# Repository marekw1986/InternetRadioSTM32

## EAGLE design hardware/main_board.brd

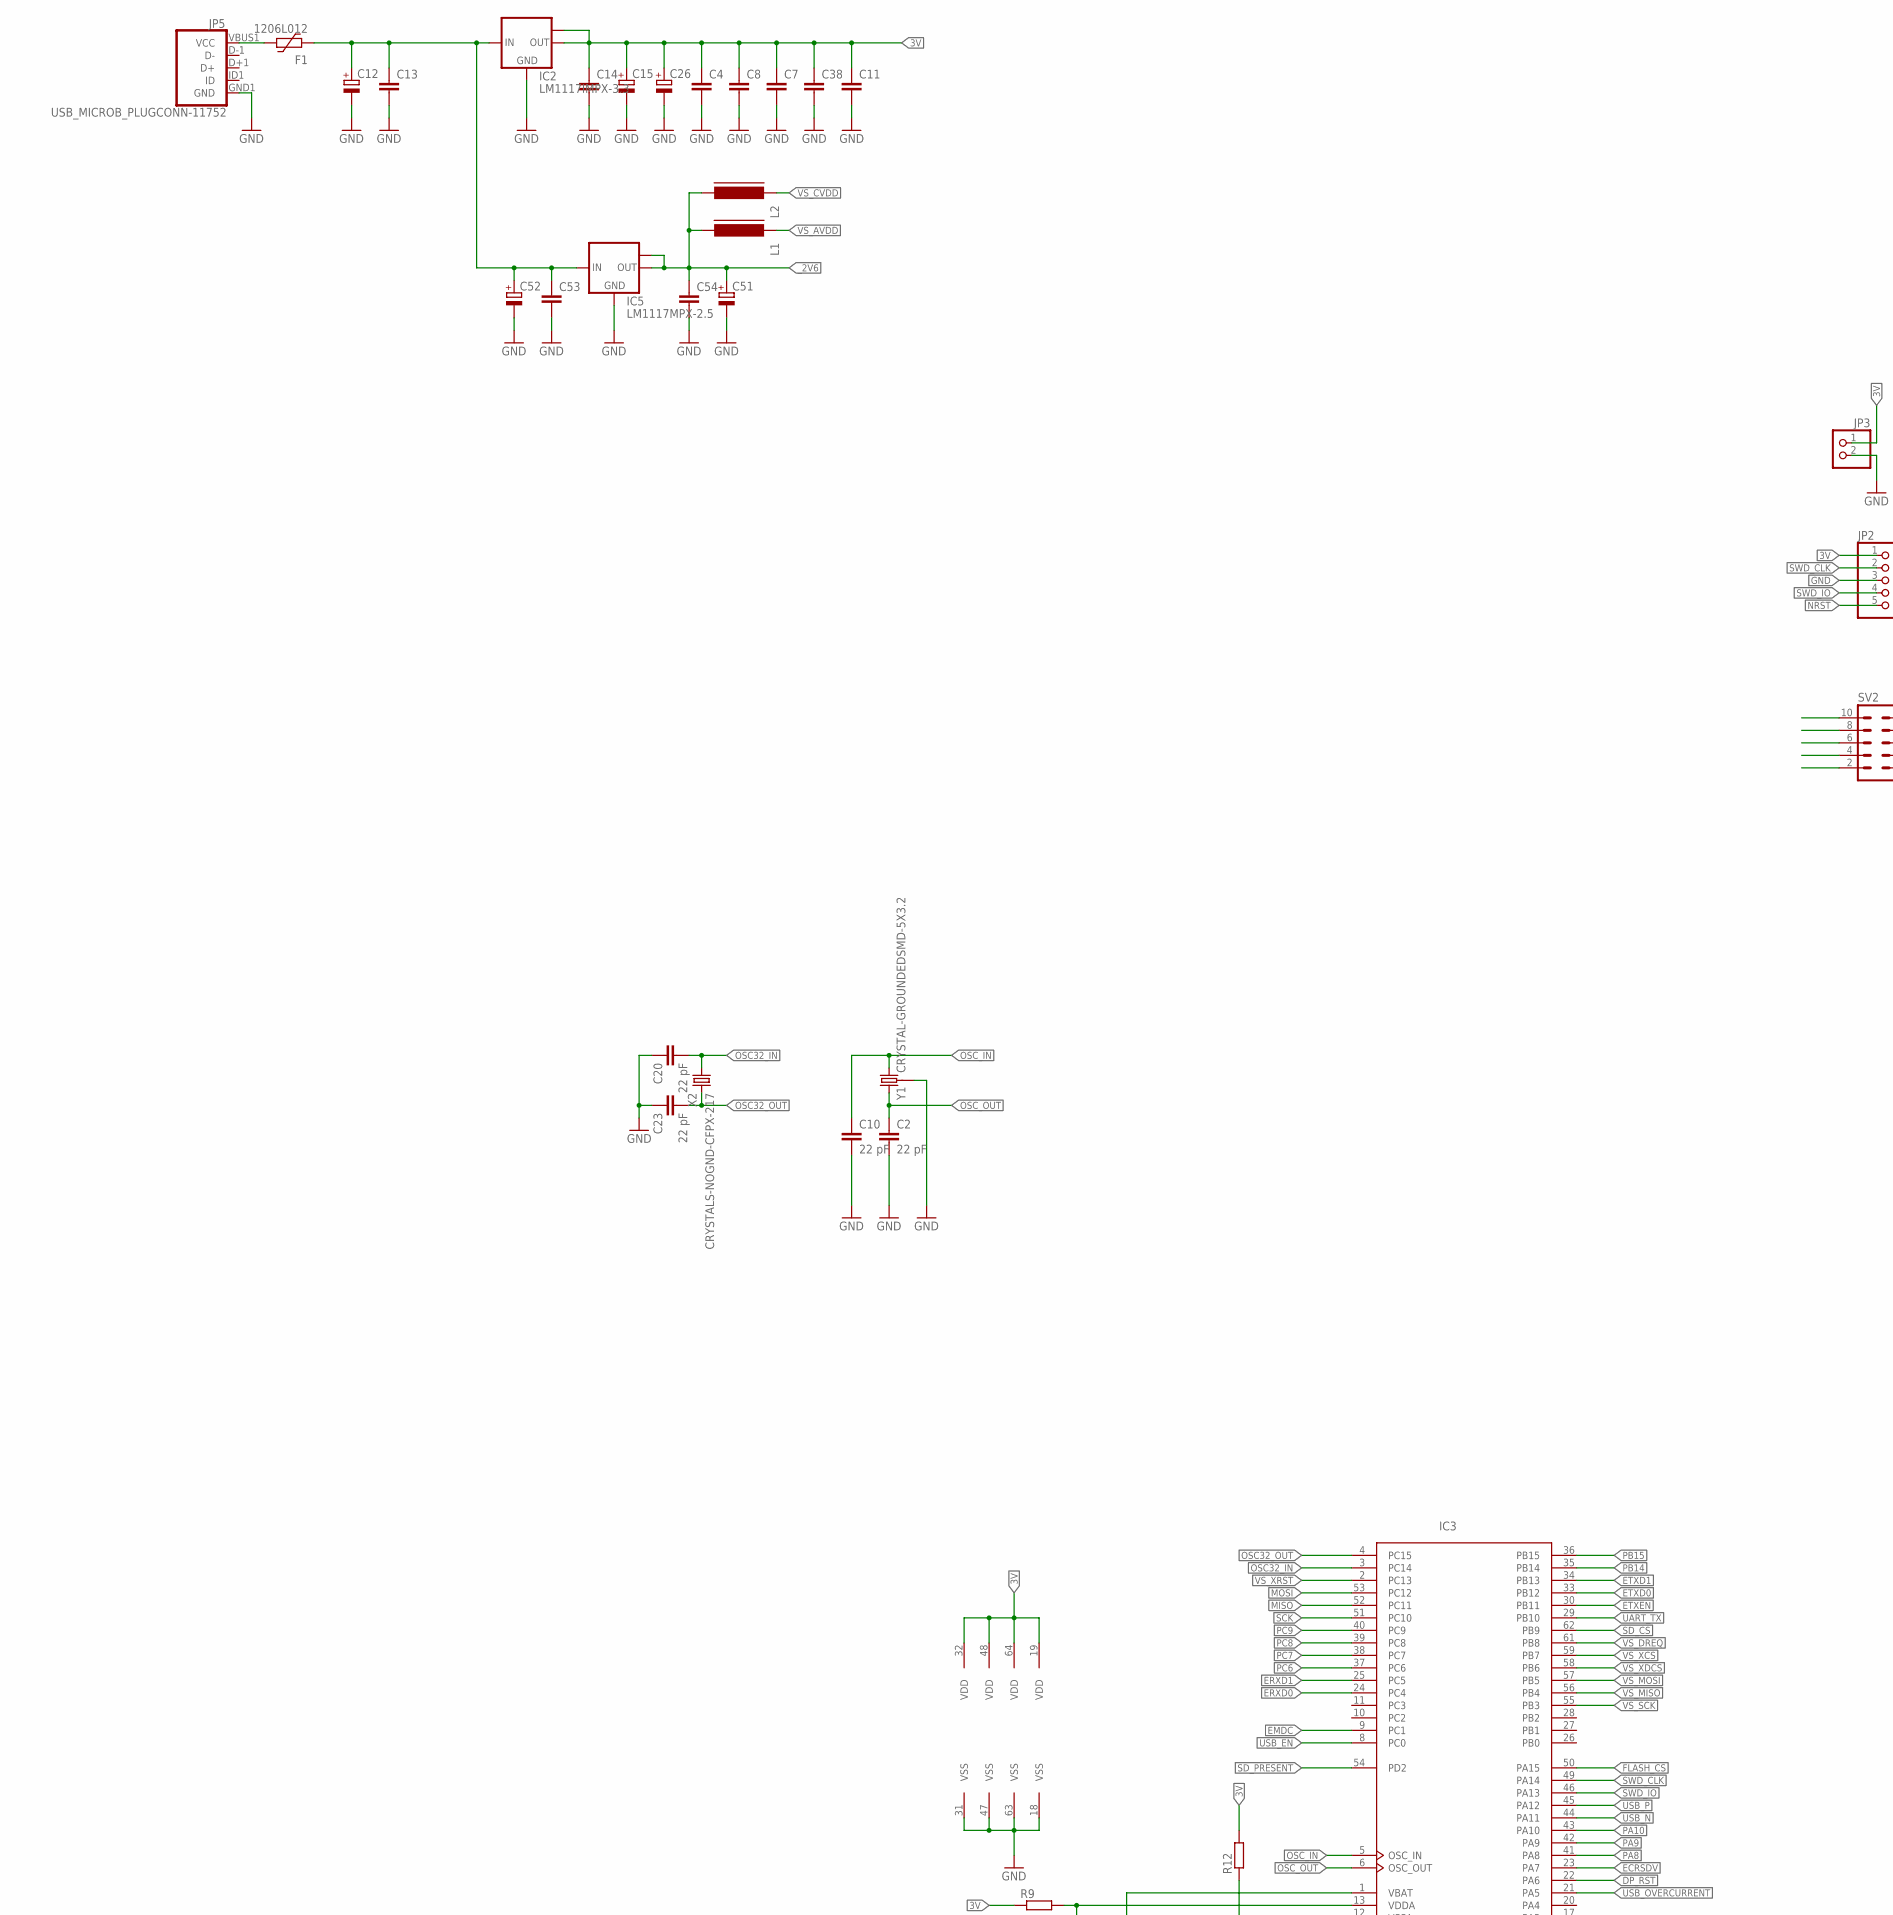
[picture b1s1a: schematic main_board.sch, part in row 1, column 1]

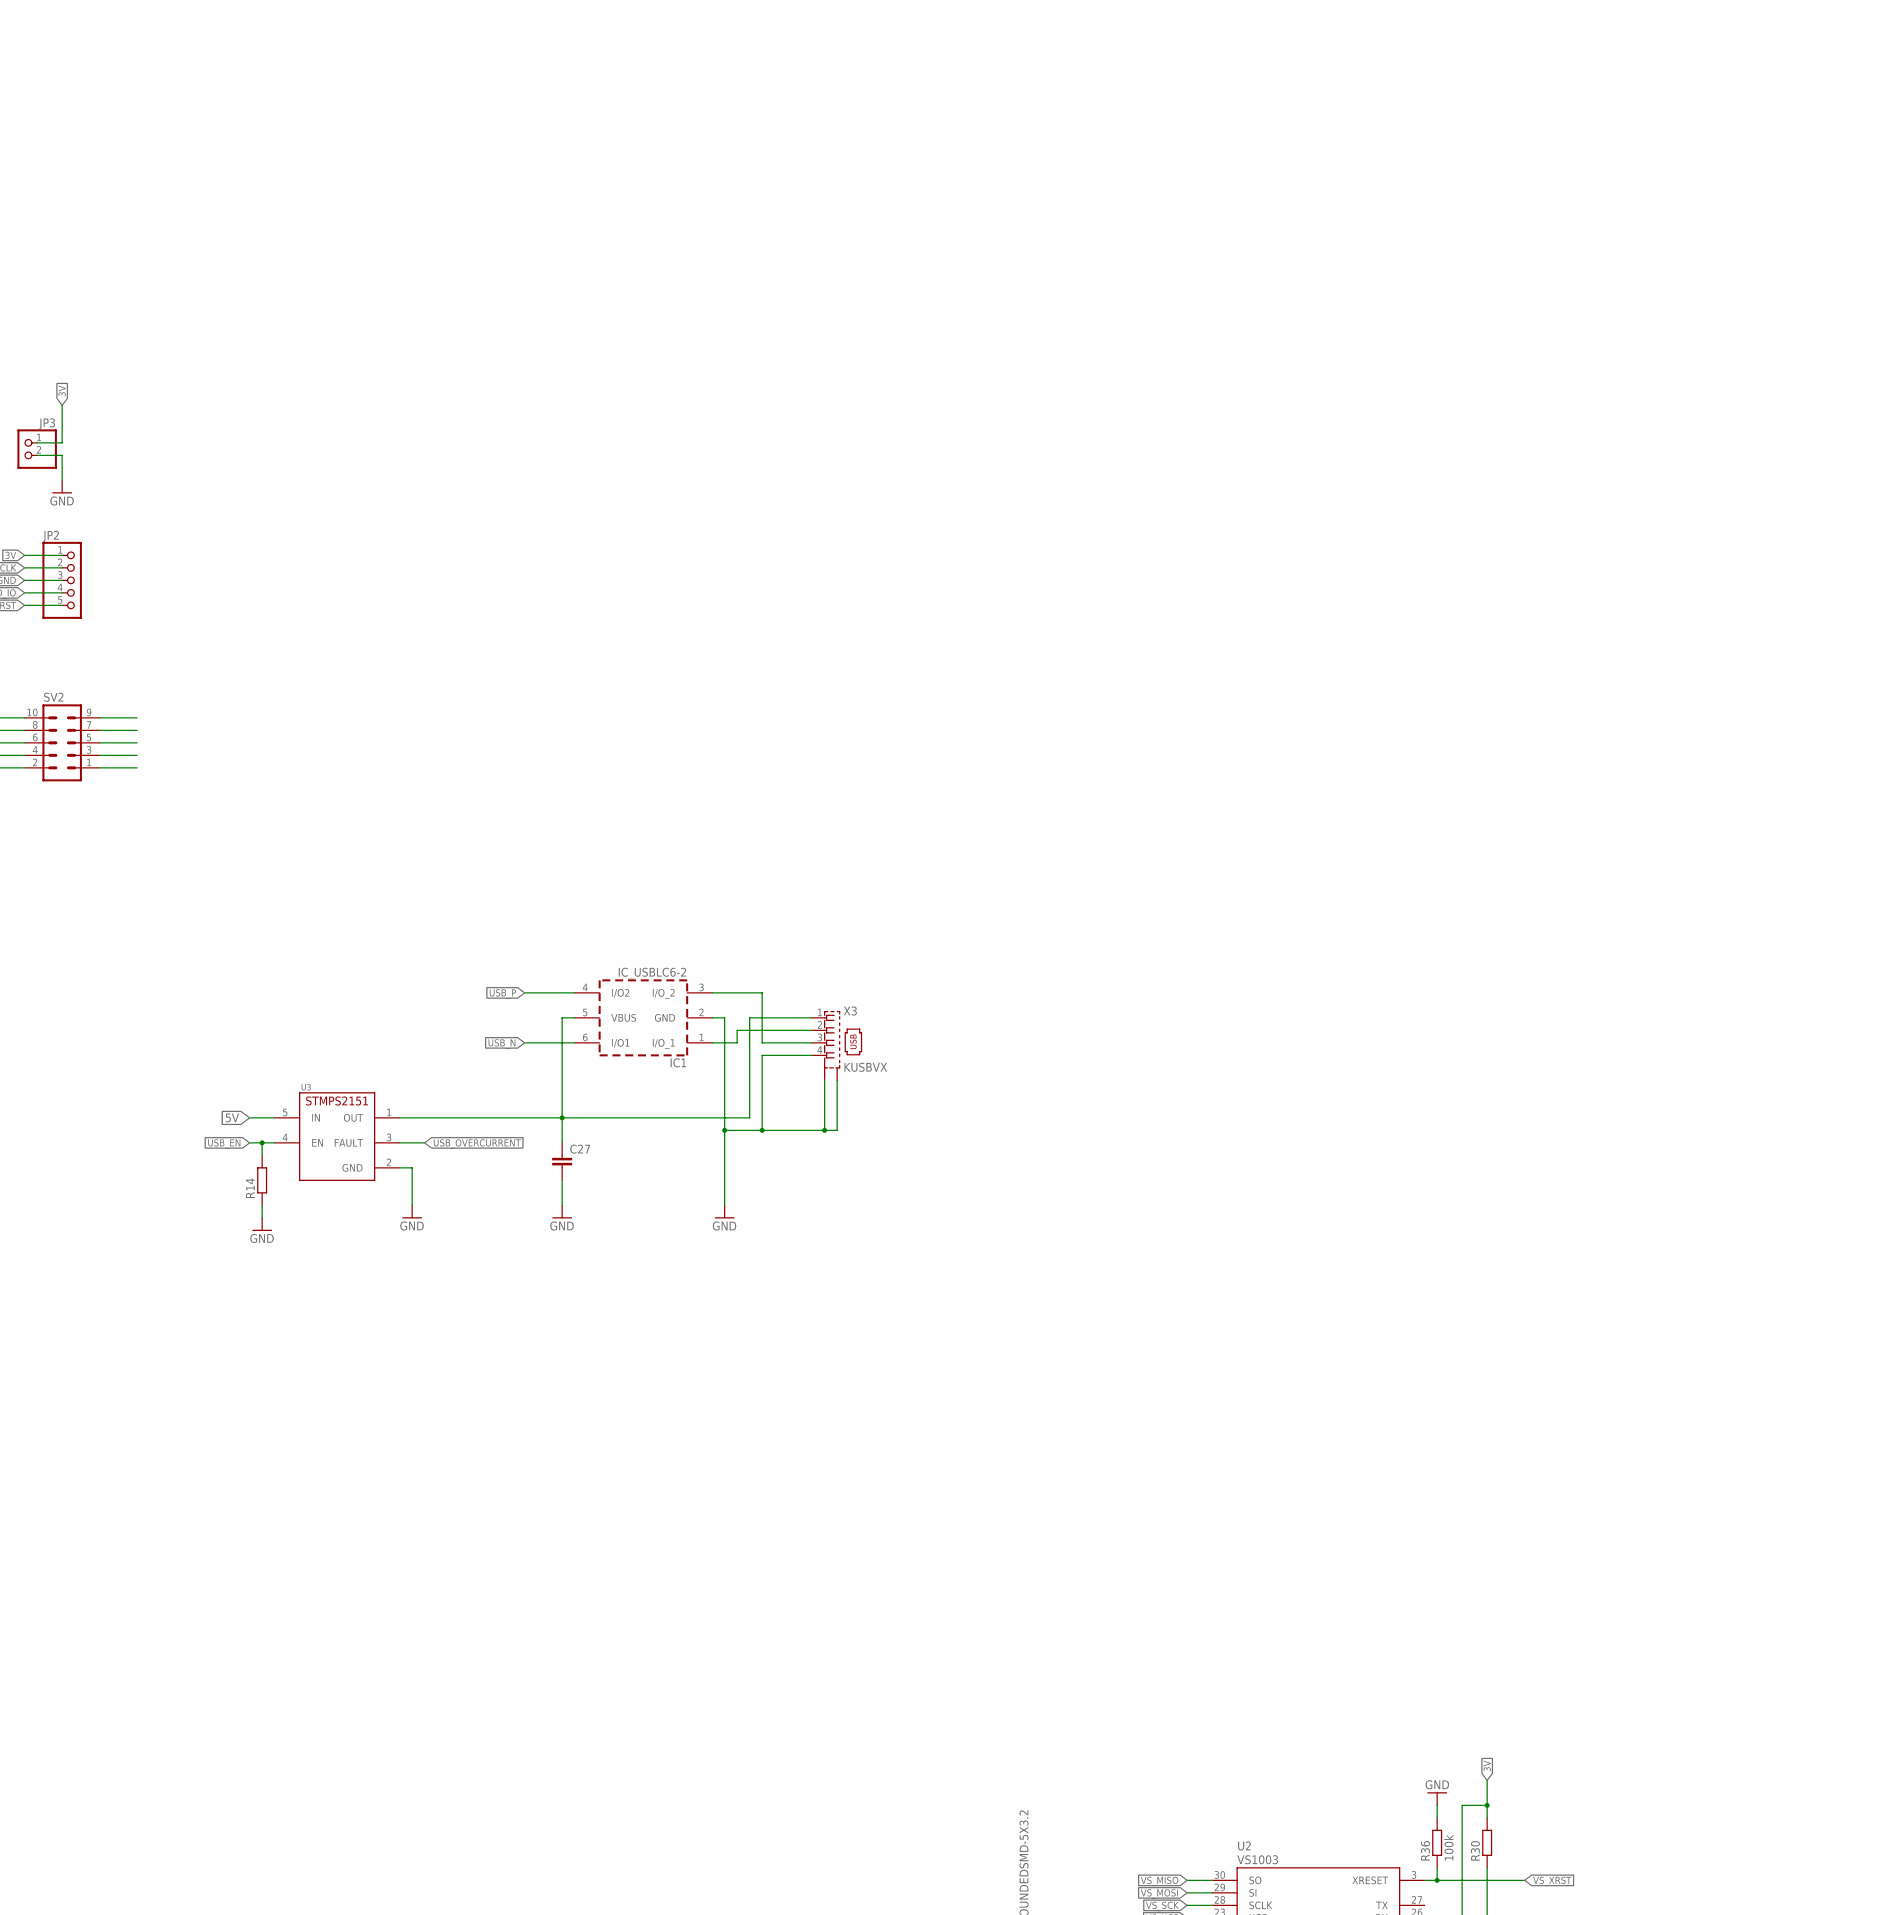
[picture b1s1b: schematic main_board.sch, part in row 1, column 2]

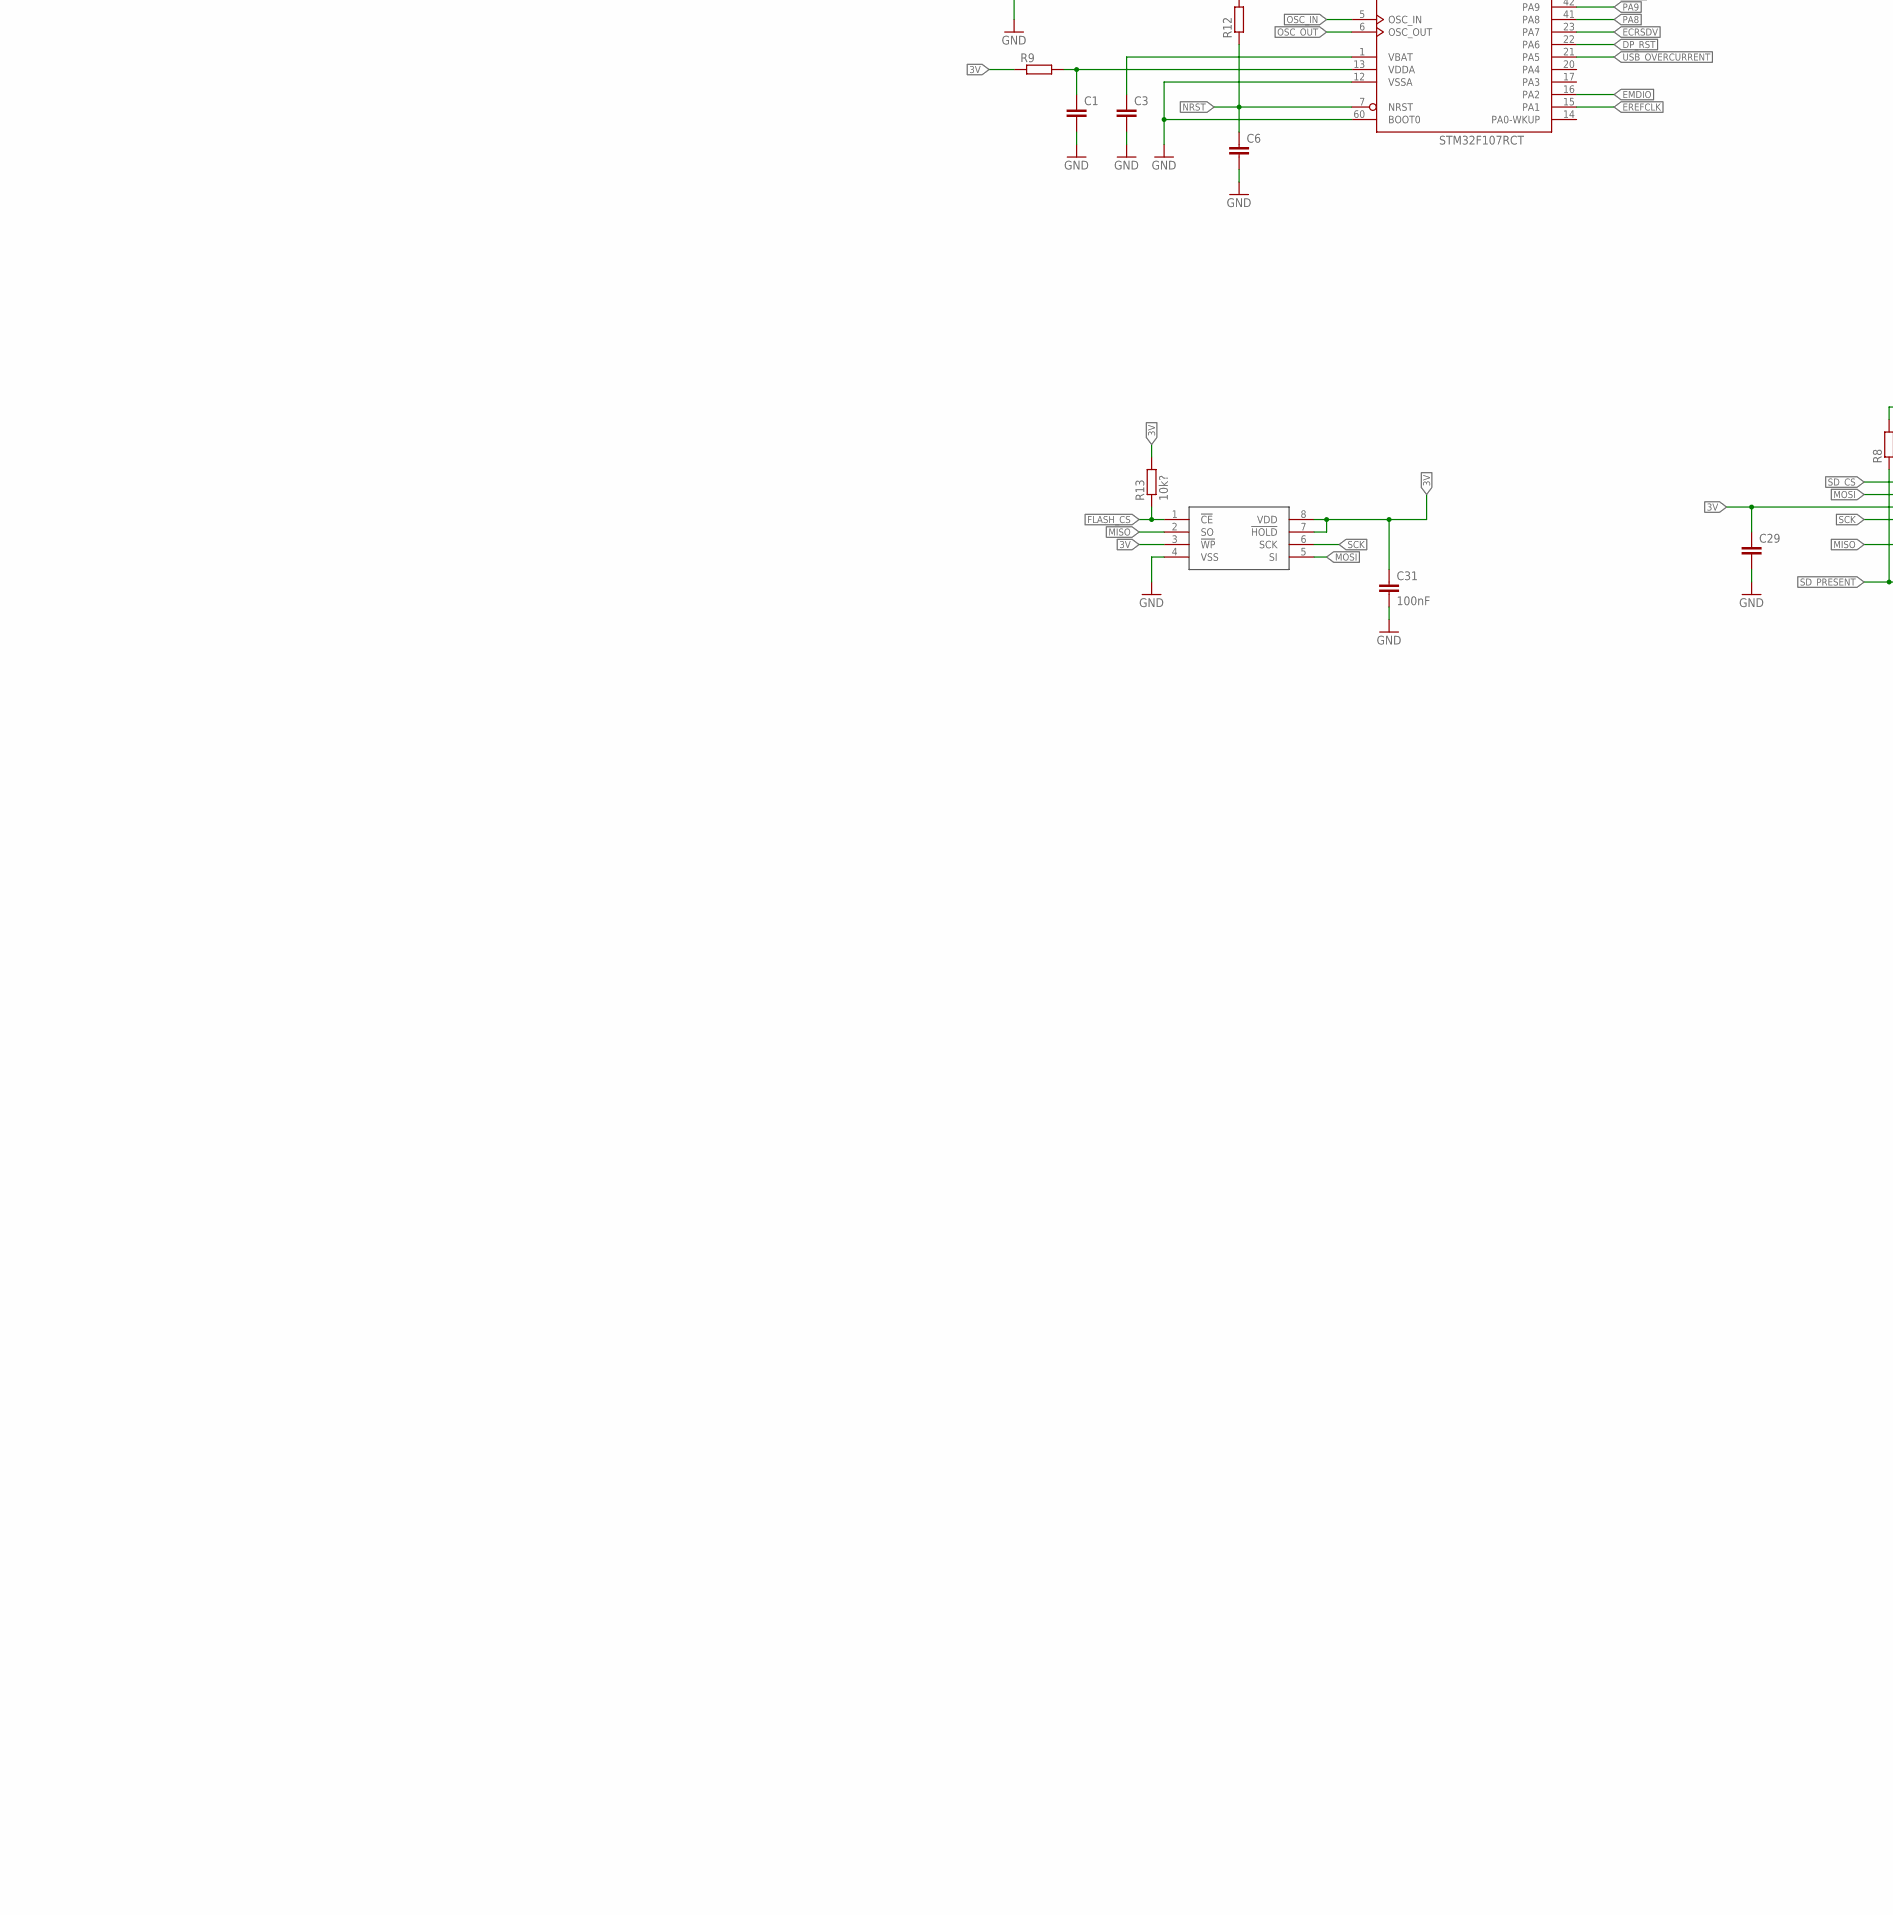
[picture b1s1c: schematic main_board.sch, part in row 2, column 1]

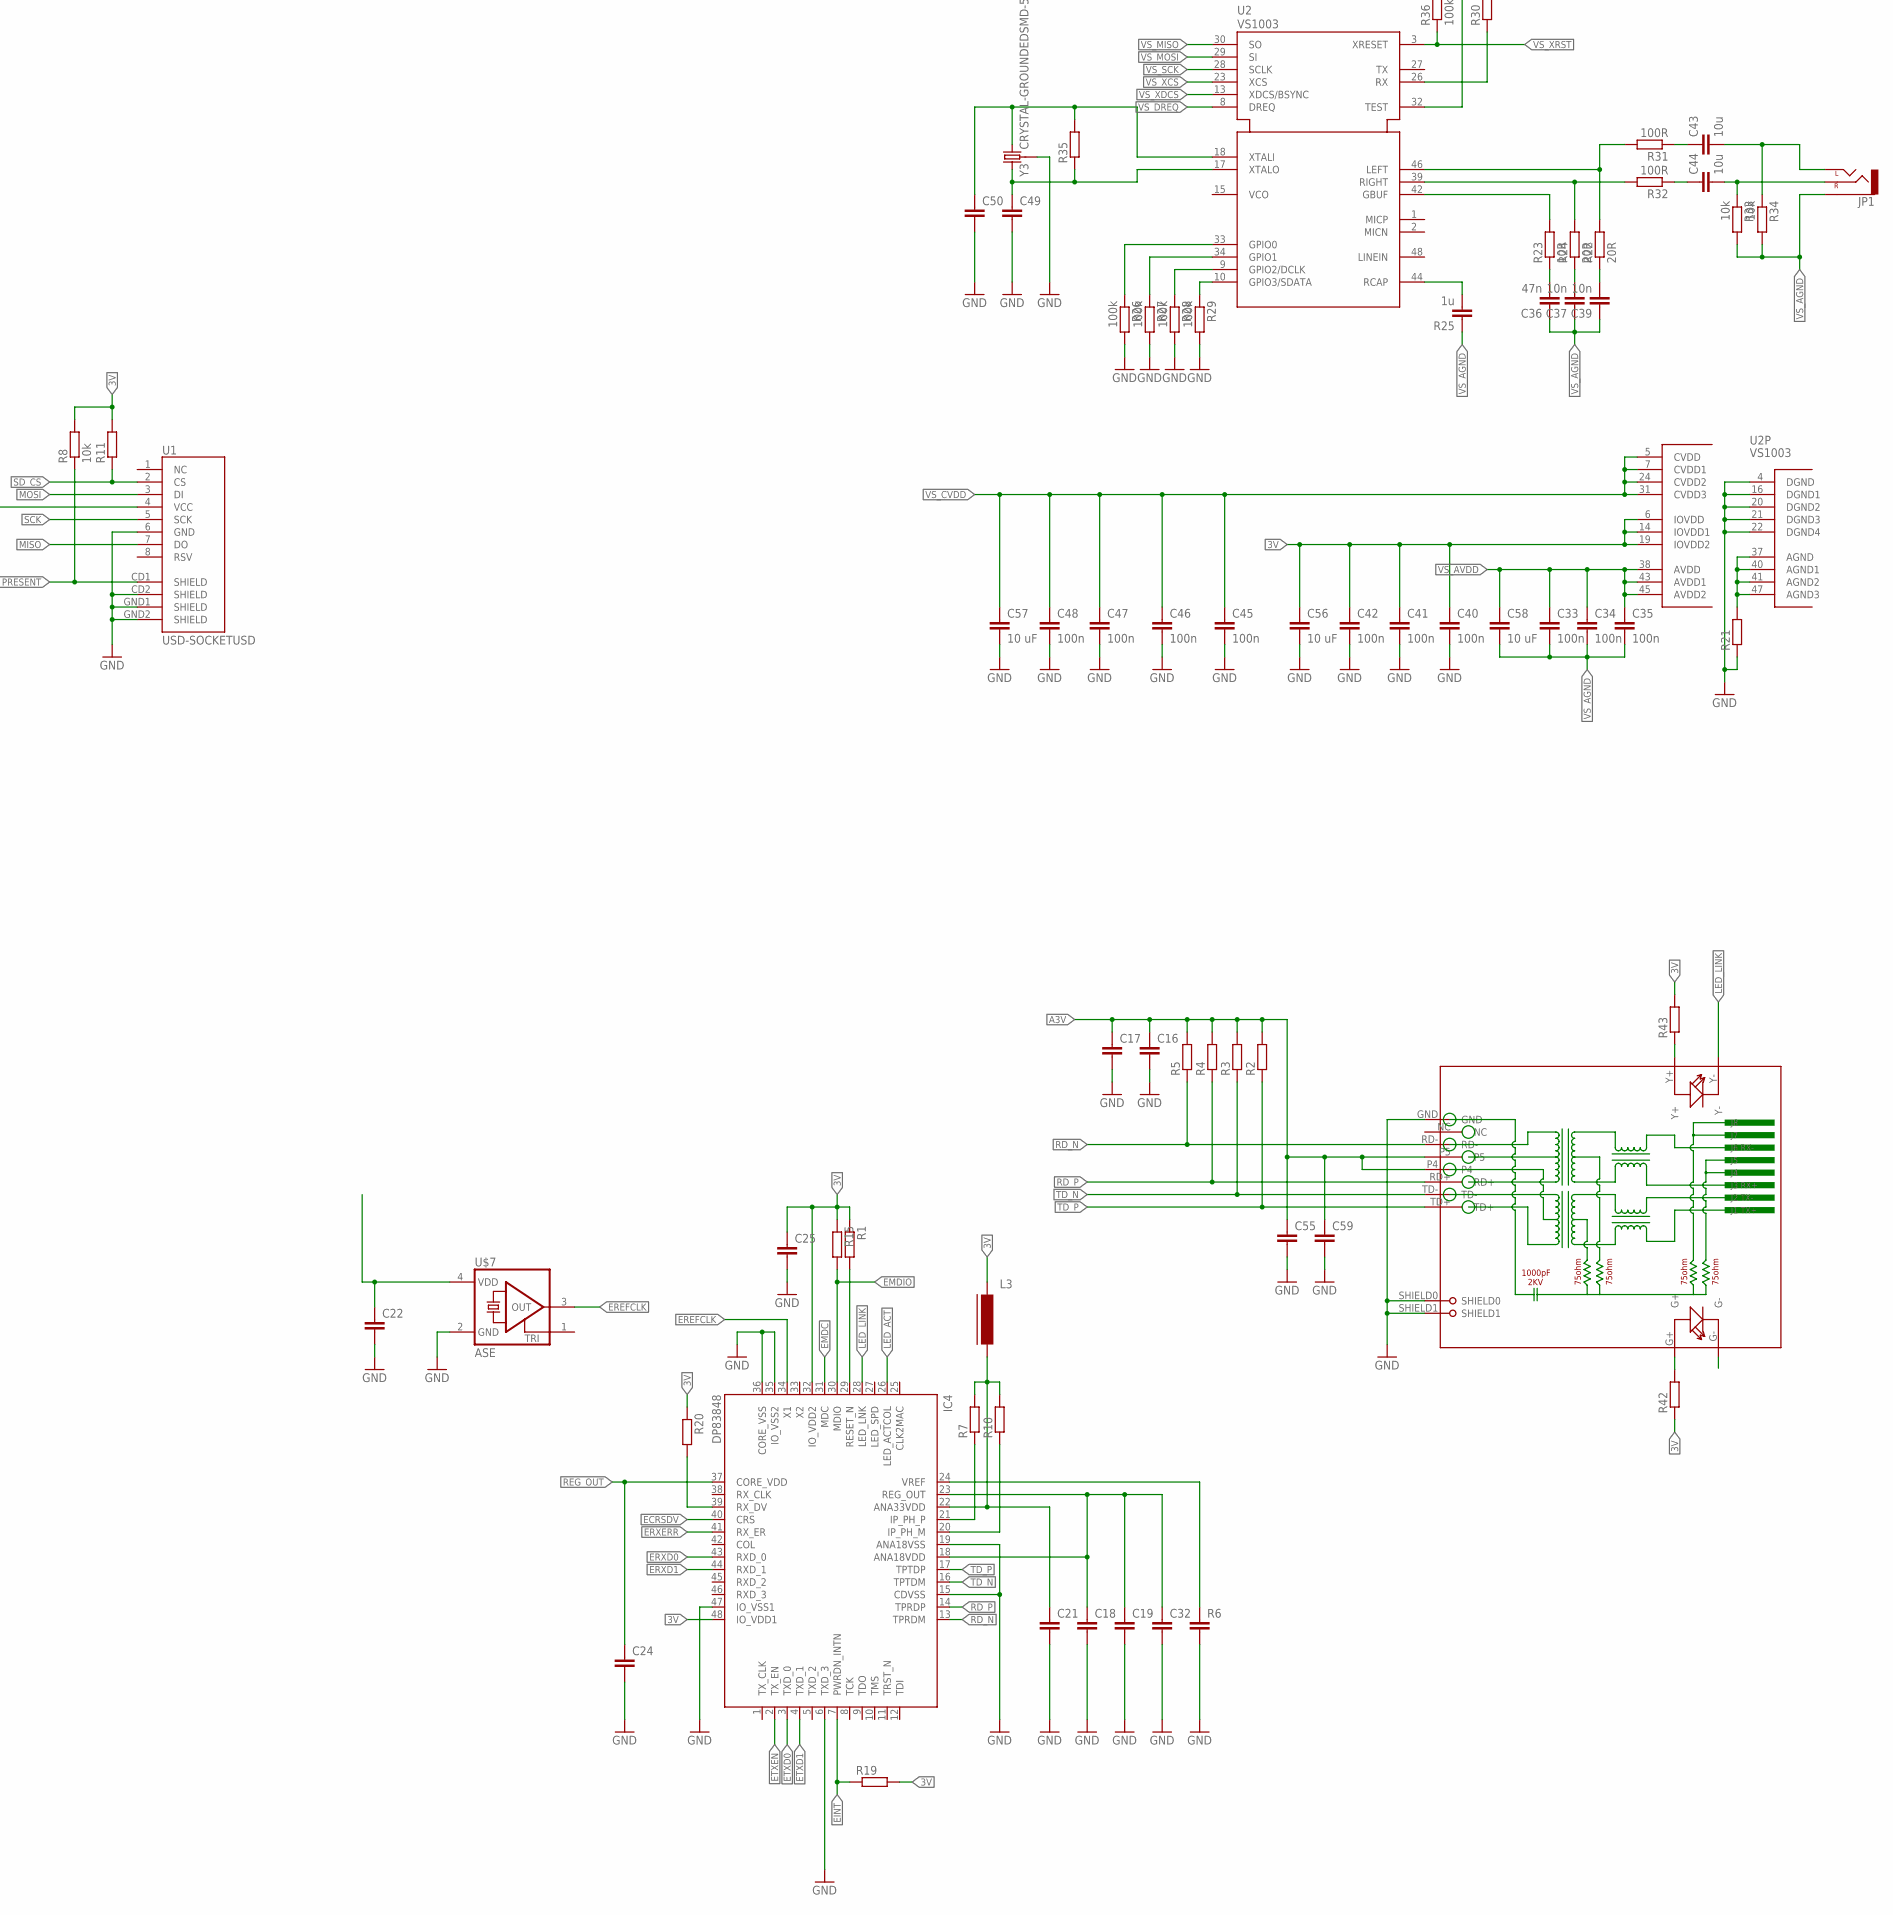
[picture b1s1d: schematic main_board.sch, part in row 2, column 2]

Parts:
C1, C3, C4, C7, C8, C11, C18, C19, C21, C22, C38: C-EUC0402; C0402
C2, C10, C20, C23: 22 pF; C0603
C6, C13, C14, C16, C17, C24, C25, C27, C29, C32, C49, C50, C55, C59: C-EUC0603; C0603
C12, C15, C51, C52: CPOL-EUSMCB; SMC_B
C26: CPOL-EUSMCA; SMC_A
C31: 100nF; C0603
C33, C34, C35, C46, C47, C48: 100n; C0603
C36: 47n; C0603
C37, C39: 10n; C0603
C40, C41, C42, C45: 100n; C0402
C43, C44: 10u; C0603
C53, C54: C-EUC1206; C1206
C56, C57, C58: 10 uF; C0603
F1: 1206L012; 1206L
IC1: IC_USBLC6-2; SOT-23-6L
IC2: LM1117IMPX-3.3; SOT223
IC3: STM32F107RCT; LQFP64
IC4: DP83848; LQFP48
IC5: LM1117MPX-2.5; SOT223
JP1: AUDIO-JACKAUDIO_JACK2; AUDIO-JACK2
JP2: PINHD-1X5; 1X05
JP3: PINHD-1X2/90; 1X02/90
JP5: USB_MICROB_PLUGCONN-11752; USB-B-MICRO-SMD_V03
L1, L2, L3: FERRITE-0805; FB805
R1, R7, R10, R19: R-EU_R0402; R0402
R2, R3, R4, R5, R11, R12, R14, R15, R20, R21, R35, R42, R43: R-EU_R0603; R0603
R6: C-EUC0603; C0603
R8, R33, R34: 10k; R0603
R9: R-EU_M0805; M0805
R13: 10k?; R0603
R22, R24: 20R; R0603
R23: 10R; R0603
R25: 1u; C0603
R26, R27, R28, R29: 100k; R0402
R30: R-EU_0204/7; 0204/7
R31, R32: 100R; R0603
R36: 100k; R0603
RJ1: HR911105A
SV2: ML10L
U1: USD-SOCKETUSD; USD-SOCKET-PP
U2: VS1003; LQFP48
U3: STMPS2151STR; SOT-23-5L
U$2: SST25VF016BSO8M; SO-08M
U$7: ASE
X2: CRYSTALS-NOGND-CFPX-217; 3.2X1.5-2-PAD
X3: KUSBVX
Y1, Y3: CRYSTAL-GROUNDEDSMD-5X3.2; CRYSTAL-SMD-5X3.2-4PAD

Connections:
3V: C4.1, C7.1, C8.1, C11.1, C14.1, C15.+, C22.1, C25.1, C26.+, C29.1, C31.1, C38.1, C40.1, C41.1, C42.1, C56.1, IC2.2 (OUT), IC2.TAB (OUT1), IC3.19 (VDD), IC3.32 (VDD), IC3.48 (VDD), IC3.64 (VDD), IC4.32 (IO_VDD2), IC4.48 (IO_VDD1), JP2.1, JP3.1, L3.1, R1.1, R8.2, R9.1, R11.2, R12.2, R13.2, R15.1, R19.2, R20.1, R30.2, R42.1, R43.2, U1.4 (VCC), U2.6 (IOVDD), U2.14 (IOVDD1), U2.19 (IOVDD2), U2.32 (TEST), U$2.3 (!WP), U$2.7 (!HOLD), U$2.8 (VDD), U$7.4 (VDD)
5V: C12.+, C13.1, C52.+, C53.1, F1.2, IC2.3 (IN), IC5.3 (IN), U3.5 (IN)
A3V: C16.1, C17.1, C21.1, C55.1, C59.1, IC4.22 (ANA33VDD), L3.2, R2.2, R3.2, R4.2, R5.2, R7.2, R10.2, RJ1.P4, RJ1.P5
D2_N: IC1.1 (I/O_1), X3.2
D2_P: IC1.3 (I/O_2), X3.3
DP_RST: IC3.22 (PA6), IC4.29 (RESET_N), R1.2
ECRSDV: IC3.23 (PA7), IC4.40 (CRS)
EINT: IC4.7 (PWRDN_INTN), R19.1
EMDC: IC3.9 (PC1), IC4.31 (MDC)
EMDIO: IC3.16 (PA2), IC4.30 (MDIO), R15.2
EREFCLK: IC3.15 (PA1), IC4.34 (X1), U$7.3 (OUT)
ERXD0: IC3.24 (PC4), IC4.43 (RXD_0)
ERXD1: IC3.25 (PC5), IC4.44 (RXD_1)
ERXERR: IC4.41 (RX_ER)
ETXD0: IC3.33 (PB12), IC4.3 (TXD_0)
ETXD1: IC3.34 (PB13), IC4.4 (TXD_1)
ETXEN: IC3.30 (PB11), IC4.2 (TX_EN)
FLASH_CS: IC3.50 (PA15), R13.1, U$2.1 (!CE)
GND: C1.2, C2.2, C3.2, C4.2, C6.2, C7.2, C8.2, C10.2, C11.2, C12.-, C13.2, C14.2, C15.-, C16.2, C17.2, C18.2, C19.2, C20.1, C21.2, C22.2, C23.1, C24.2, C25.2, C26.-, C27.2, C29.2, C31.2, C32.2, C38.2, C40.2, C41.2, C42.2, C45.2, C46.2, C47.2, C48.2, C49.2, C50.2, C51.-, C52.-, C53.2, C54.2, C55.2, C56.2, C57.2, C59.2, IC1.2 (GND), IC2.1 (GND), IC3.12 (VSSA), IC3.18 (VSS), IC3.31 (VSS), IC3.47 (VSS), IC3.60 (BOOT0), IC3.63 (VSS), IC4.6 (TXD_3), IC4.15 (CDVSS), IC4.19 (ANA18VSS), IC4.35 (IO_VSS2), IC4.36 (CORE_VSS), IC4.47 (IO_VSS1), IC5.1 (GND), JP2.3, JP3.2, JP5.GND1 (GND), R6.2, R14.1, R21.1, R26.2, R27.2, R28.2, R29.2, R36.2, RJ1.GND, RJ1.SHIELD0, RJ1.SHIELD1, U1.6 (GND), U1.CD2 (SHIELD), U1.GND1 (SHIELD), U1.GND2 (SHIELD), U2.4 (DGND)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
LED_ACT: IC4.26 (LED_ACTCOL), RJ1.G-
LED_LINK: IC4.28 (LED_LNK), RJ1.Y-
MISO: IC3.52 (PC11), U1.7 (DO), U$2.2 (SO)
MOSI: IC3.53 (PC12), U1.3 (DI), U$2.5 (SI)
unnamed: IC4.21 (IP_PH_P), R7.1
unnamed: C3.1, IC3.1 (VBAT)
unnamed: IC4.24 (VREF), R6.1
unnamed: IC4.20 (IP_PH_M), R10.1
unnamed: R42.2, RJ1.G+
unnamed: F1.1, JP5.VBUS1 (VCC)
unnamed: C36.2, R23.1
unnamed: R43.1, RJ1.Y+
unnamed: C1.1, IC3.13 (VDDA), R9.2
NRST: C6.1, IC3.7 (NRST), JP2.5, R12.1
OSC32_IN: C20.2, IC3.3 (PC14), X2.1
OSC32_OUT: C23.2, IC3.4 (PC15), X2.2
OSC_IN: C10.1, IC3.5 (OSC_IN), Y1.1 (2)
OSC_OUT: C2.1, IC3.6 (OSC_OUT), Y1.3 (1)
PA8: IC3.41 (PA8), SV2.8
PA9: IC3.42 (PA9), SV2.9
PA10: IC3.43 (PA10), SV2.10
PB14: IC3.35 (PB14), SV2.2
PB15: IC3.36 (PB15), SV2.3
PC6: IC3.37 (PC6), SV2.4
PC7: IC3.38 (PC7), SV2.5
PC8: IC3.39 (PC8), SV2.6
PC9: IC3.40 (PC9), SV2.7
RD_N: IC4.13 (TPRDM), R5.1, RJ1.RD-
RD_P: IC4.14 (TPRDP), R4.1, RJ1.RD+
REG_OUT: C18.1, C19.1, C24.1, C32.1, IC4.18 (ANA18VDD), IC4.23 (REG_OUT), IC4.37 (CORE_VDD)
RX_DV: IC4.39 (RX_DV), R20.2
SCK: IC3.51 (PC10), U1.5 (SCK), U$2.6 (SCK)
SD_CS: IC3.62 (PB9), R11.1, U1.2 (CS)
SD_PRESENT: IC3.54 (PD2), R8.1, U1.CD1 (SHIELD)
SWD_CLK: IC3.49 (PA14), JP2.2
SWD_IO: IC3.46 (PA13), JP2.4
TD_N: IC4.16 (TPTDM), R3.1, RJ1.TD-
TD_P: IC4.17 (TPTDP), R2.1, RJ1.TD+
UART_TX: IC3.29 (PB10), SV2.1
USB_EN: IC3.8 (PC0), R14.2, U3.4 (EN)
USB_N: IC1.6 (I/O1), IC3.44 (PA11)
USB_OVERCURRENT: IC3.21 (PA5), U3.3 (FAULT)
USB_P: IC1.4 (I/O2), IC3.45 (PA12)
VBUS: C27.1, IC1.5 (VBUS), U3.1 (OUT), X3.1
VS_AGND: C33.2, C34.2, C35.2, C36.1, C37.1, C39.1, C58.2, JP1.SLEEVE, R21.2, R25.1, R33.2, R34.2, U2.37 (AGND), U2.40 (AGND1), U2.41 (AGND2), U2.47 (AGND3)
VS_AVDD: C33.1, C34.1, C35.1, C58.1, L1.1, U2.38 (AVDD), U2.43 (AVDD1), U2.45 (AVDD2)
VS_CVDD: C45.1, C46.1, C47.1, C48.1, C57.1, L2.1, U2.5 (CVDD), U2.7 (CVDD1), U2.24 (CVDD2), U2.31 (CVDD3)
VS_DREQ: IC3.61 (PB8), U2.8 (DREQ)
VS_MISO: IC3.56 (PB4), U2.30 (SO)
VS_MOSI: IC3.57 (PB5), U2.29 (SI)
VS_N$9: C50.1, R35.2, U2.18 (XTALI), Y3.1 (2)
VS_N$13: C49.1, R35.1, U2.17 (XTALO), Y3.3 (1)
VS_N$14: R22.2, R31.2, U2.46 (LEFT)
VS_N$15: R23.2, U2.42 (GBUF)
VS_N$16: R24.2, R32.2, U2.39 (RIGHT)
VS_N$17: R25.2, U2.44 (RCAP)
VS_N$24: C37.2, R24.1
VS_N$25: C39.2, R22.1
VS_N$26: R29.1, U2.10 (GPIO3/SDATA)
VS_N$27: R28.1, U2.9 (GPIO2/DCLK)
VS_N$28: R27.1, U2.34 (GPIO1)
VS_N$30: R26.1, U2.33 (GPIO0)
VS_N$34: R30.1, U2.26 (RX)
VS_N$35: C43.1, R31.1
VS_N$36: C44.1, R32.1
VS_N$37: C44.2, JP1.RING (RIGHT), R33.1
VS_N$38: C43.2, JP1.TIP (LEFT), R34.1
VS_SCK: IC3.55 (PB3), U2.28 (SCLK)
VS_XCS: IC3.59 (PB7), U2.23 (XCS)
VS_XDCS: IC3.58 (PB6), U2.13 (XDCS/BSYNC)
VS_XRST: IC3.2 (PC13), R36.1, U2.3 (XRESET)
_2V6: C51.+, C54.1, IC5.2 (OUT), IC5.TAB (OUT1), L1.2, L2.2

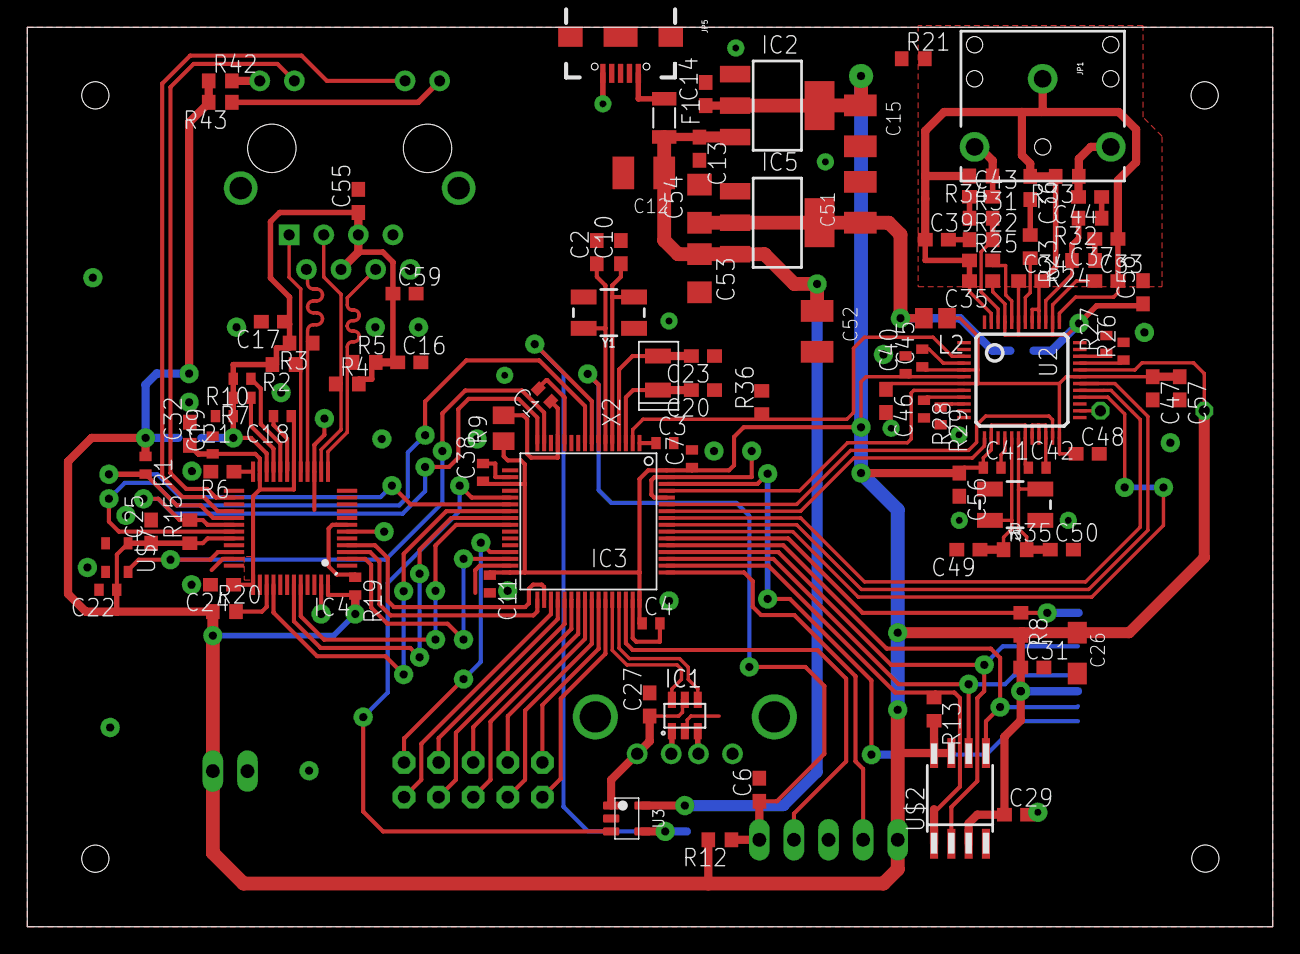
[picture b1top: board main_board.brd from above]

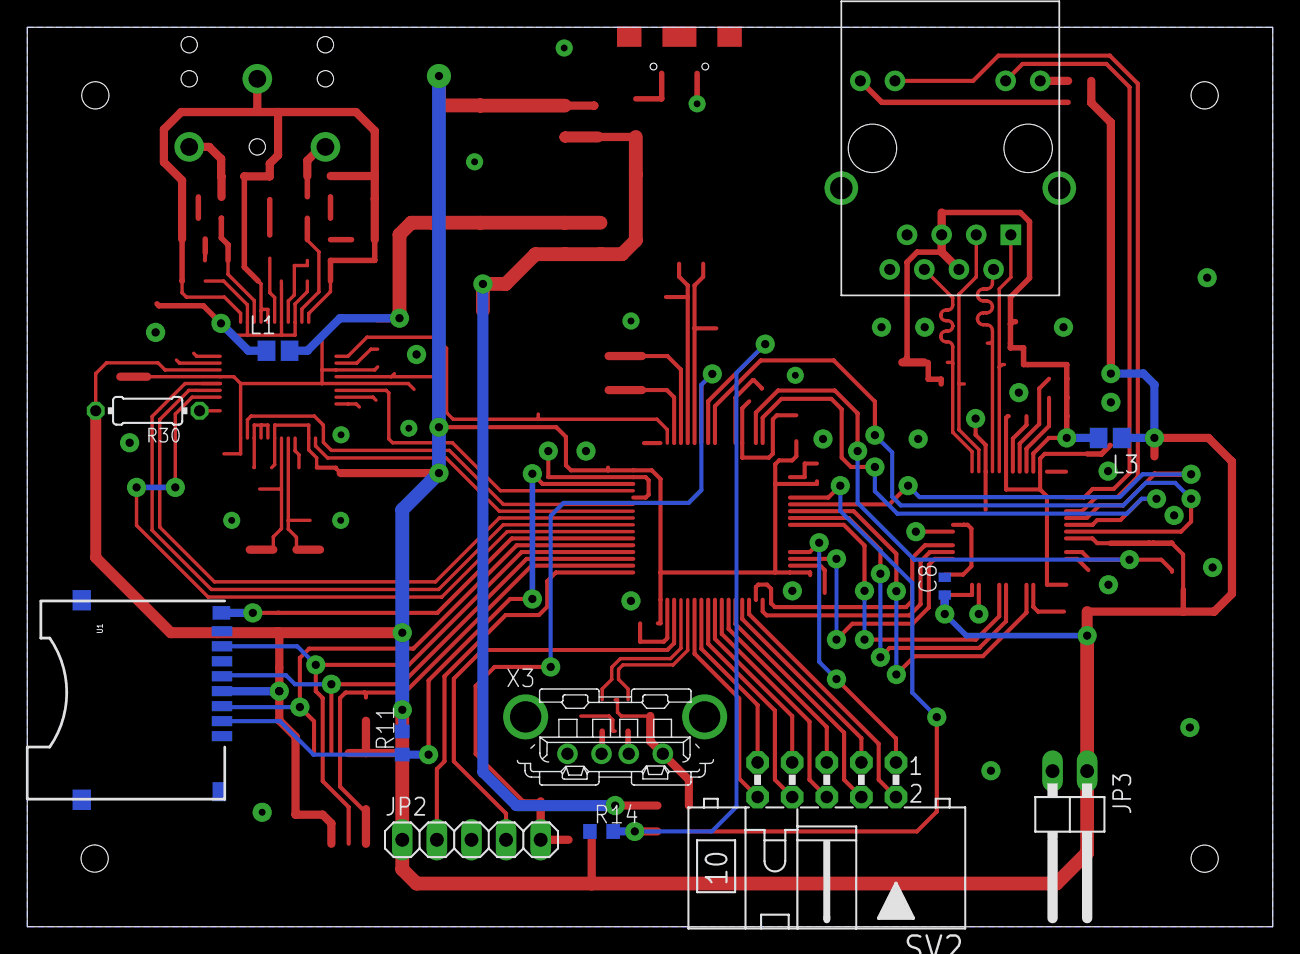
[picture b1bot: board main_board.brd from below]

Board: 2 copper layers, 91.4 x 66.0 mm, 114 parts (12 on the bottom side), 90 nets.

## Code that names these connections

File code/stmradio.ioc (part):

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Mcu.Name=STM32F107R(B-C)Tx
Mcu.Package=LQFP64
Mcu.UserName=STM32F107RCTx
PA1.Mode=RMII
PA1.Signal=ETH_REF_CLK
PA11.Mode=Host_Only
PA11.Signal=USB_OTG_FS_DM
PA12.Mode=Host_Only
PA12.Signal=USB_OTG_FS_DP
PA13.Mode=Serial_Wire
PA13.Signal=SYS_JTMS-SWDIO
PA14.Mode=Serial_Wire
PA14.Signal=SYS_JTCK-SWCLK
PA15.GPIOParameters=GPIO_Label
PA15.GPIO_Label=FLASH_CS
PA15.Signal=GPIO_Output
PA2.Mode=RMII
PA2.Signal=ETH_MDIO
PA5.GPIOParameters=GPIO_Label
PA5.GPIO_Label=USB_OVERCURRENT
PA5.Signal=GPIO_Input
PA6.GPIOParameters=GPIO_Label
PA6.GPIO_Label=DP_RST
PA6.Signal=GPIO_Output
PA7.Mode=RMII
PA7.Signal=ETH_CRS_DV
PB10.Mode=Half_duplex(single_wire_mode)
PB10.Signal=USART3_TX
PB11.Mode=RMII
PB11.Signal=ETH_TX_EN
PB12.Mode=RMII
PB12.Signal=ETH_TXD0
PB13.Mode=RMII
PB13.Signal=ETH_TXD1
PB3.Mode=Full_Duplex_Master
PB3.Signal=SPI1_SCK
PB4.Mode=Full_Duplex_Master
PB4.Signal=SPI1_MISO
PB5.Mode=Full_Duplex_Master
PB5.Signal=SPI1_MOSI
PB6.GPIOParameters=GPIO_Label
PB6.GPIO_Label=VS_XDCS
PB6.Signal=GPIO_Output
PB7.GPIOParameters=GPIO_Label
PB7.GPIO_Label=VS_XCS
PB7.Signal=GPIO_Output
PB8.GPIOParameters=GPIO_Label
PB8.GPIO_Label=VS_DREQ
PB8.Signal=GPIO_Input
PB9.GPIOParameters=GPIO_Label
PB9.GPIO_Label=SD_CS
PB9.Signal=GPIO_Output
PC0.GPIOParameters=GPIO_Label
PC0.GPIO_Label=USB_EN
PC0.Signal=GPIO_Output
PC1.Mode=RMII
PC1.Signal=ETH_MDC
PC10.Mode=Full_Duplex_Master
PC10.Signal=SPI3_SCK
PC11.Mode=Full_Duplex_Master
PC11.Signal=SPI3_MISO
PC12.Mode=Full_Duplex_Master
PC12.Signal=SPI3_MOSI
PC13-TAMPER-RTC.GPIOParameters=GPIO_Label
PC13-TAMPER-RTC.GPIO_Label=VS_XRST
PC13-TAMPER-RTC.Signal=GPIO_Output
PC14-OSC32_IN.Mode=LSE-External-Oscillator
PC14-OSC32_IN.Signal=RCC_OSC32_IN
PC15-OSC32_OUT.Mode=LSE-External-Oscillator
PC15-OSC32_OUT.Signal=RCC_OSC32_OUT
PC4.Mode=RMII
PC4.Signal=ETH_RXD0
PC5.Mode=RMII
PC5.Signal=ETH_RXD1
PD0-OSC_IN.Mode=HSE-External-Oscillator
PD0-OSC_IN.Signal=RCC_OSC_IN
PD1-OSC_OUT.Mode=HSE-External-Oscillator
PD1-OSC_OUT.Signal=RCC_OSC_OUT
PD2.GPIOParameters=GPIO_Label
PD2.GPIO_Label=SD_PRESENT
PD2.Signal=GPIO_Input
RCC.SYSCLKFreq_VALUE=72000000
RCC.SYSCLKSource=RCC_SYSCLKSOURCE_PLLCLK
board=custom

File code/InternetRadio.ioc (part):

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Mcu.Name=STM32F107R(B-C)Tx
Mcu.Package=LQFP64
Mcu.UserName=STM32F107RCTx
PA1.Mode=RMII
PA1.Signal=ETH_REF_CLK
PA10.Mode=Asynchronous
PA10.Signal=USART1_RX
PA11.Mode=Host_Only
PA11.Signal=USB_OTG_FS_DM
PA12.Mode=Host_Only
PA12.Signal=USB_OTG_FS_DP
PA13.Mode=Serial_Wire
PA13.Signal=SYS_JTMS-SWDIO
PA14.Mode=Serial_Wire
PA14.Signal=SYS_JTCK-SWCLK
PA15.GPIOParameters=GPIO_Speed,PinState,GPIO_PuPd,GPIO_Label
PA15.GPIO_Label=SPIRAM_CS
PA15.GPIO_PuPd=GPIO_PULLUP
PA15.GPIO_Speed=GPIO_SPEED_FREQ_HIGH
PA15.PinState=GPIO_PIN_SET
PA15.Signal=GPIO_Output
PA2.Mode=RMII
PA2.Signal=ETH_MDIO
PA5.GPIOParameters=GPIO_Label
PA5.GPIO_Label=USB_OVERCURRENT
PA5.Signal=GPIO_Input
PA7.Mode=RMII
PA7.Signal=ETH_CRS_DV
PA9.Mode=Asynchronous
PA9.Signal=USART1_TX
PB10.GPIOParameters=GPIO_Label
PB10.GPIO_Label=TST
PB10.Signal=GPIO_Output
PB11.Mode=RMII
PB11.Signal=ETH_TX_EN
PB12.Mode=RMII
PB12.Signal=ETH_TXD0
PB13.Mode=RMII
PB13.Signal=ETH_TXD1
PB14.GPIOParameters=GPIO_PuPd,GPIO_Label
PB14.GPIO_Label=NEXT_BTN
PB14.GPIO_PuPd=GPIO_PULLUP
PB14.Signal=GPIO_Input
PB3.Mode=Full_Duplex_Master
PB3.Signal=SPI1_SCK
PB4.GPIOParameters=GPIO_PuPd
PB4.GPIO_PuPd=GPIO_PULLUP
PB4.Mode=Full_Duplex_Master
PB4.Signal=SPI1_MISO
PB5.Mode=Full_Duplex_Master
PB5.Signal=SPI1_MOSI
PB6.GPIOParameters=GPIO_Label
PB6.GPIO_Label=VS_XDCS
PB6.Signal=GPIO_Output
PB7.GPIOParameters=GPIO_Label
PB7.GPIO_Label=VS_XCS
PB7.Signal=GPIO_Output
PB8.GPIOParameters=GPIO_Label
PB8.GPIO_Label=VS_DREQ
PB8.Signal=GPIO_Input
PB9.GPIOParameters=GPIO_Speed,PinState,GPIO_PuPd,GPIO_Label
PB9.GPIO_Label=SD_CS
PB9.GPIO_PuPd=GPIO_PULLUP
PB9.GPIO_Speed=GPIO_SPEED_FREQ_HIGH
PB9.PinState=GPIO_PIN_SET
PB9.Signal=GPIO_Output
PC0.GPIOParameters=GPIO_Label
PC0.GPIO_Label=USB_EN
PC0.Signal=GPIO_Output
PC1.Mode=RMII
PC1.Signal=ETH_MDC
PC10.Mode=Full_Duplex_Master
PC10.Signal=SPI3_SCK
PC11.GPIOParameters=GPIO_PuPd
PC11.GPIO_PuPd=GPIO_PULLUP
PC11.Mode=Full_Duplex_Master
PC11.Signal=SPI3_MISO
PC12.Mode=Full_Duplex_Master
PC12.Signal=SPI3_MOSI
PC13-TAMPER-RTC.GPIOParameters=GPIO_Label
PC13-TAMPER-RTC.GPIO_Label=VS_XRST
PC13-TAMPER-RTC.Signal=GPIO_Output
PC4.Mode=RMII
PC4.Signal=ETH_RXD0
PC5.Mode=RMII
PC5.Signal=ETH_RXD1
PD0-OSC_IN.Mode=HSE-External-Oscillator
PD0-OSC_IN.Signal=RCC_OSC_IN
PD1-OSC_OUT.Mode=HSE-External-Oscillator
PD1-OSC_OUT.Signal=RCC_OSC_OUT
PD2.GPIOParameters=GPIO_Label
PD2.GPIO_Label=SD_PRESENT
PD2.Signal=GPIO_Input
RCC.SYSCLKFreq_VALUE=72000000
RCC.SYSCLKSource=RCC_SYSCLKSOURCE_PLLCLK
board=custom

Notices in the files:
parts and their libraries:
SparkFun-Clocks: Licensing: Creative Commons ShareAlike 4.0 International - https://creativecommons.org/licenses/by-sa/4.0
FaBo-Supply: Released under the Creative Commons Attribution-ShareAlike 4.0 License
https://creativecommons.org/licenses/by-sa/4.0
